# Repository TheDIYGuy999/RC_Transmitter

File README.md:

# This is an Arduino 2.4GHz radio and IR transmitter for Atmel AVR
## Features:
- IR transmitter for "LEGO" Powerfunctions and trains as well as for "MECCANO" motors
- 2.4GHz radio transmitter for RC cars, helicopters etc.
- 4 analog axes, 2 mode switches (joystick buttons)
- 1 potentiometer for adjustments like the MRSC stability control
- 4 push buttons for transmission mode and vehicle selection as well as menu navigation
- 20 seletcable vehicle addresses, so you can use it for more than one vehicle
- 3.3V, 8MHz Pro Mini (a Pro Micro is not supported anymore due to additional functionality)
- STM32 ARM version (deprecated) see: https://github.com/TheDIYGuy999/RC_Transmitter_STM32
- 2.4GHz NRF24L01 radio module
- Support for 0.96" I2C OLED
- Configuration menu for: Channel direction reversing, servo travel adjustment (independent for each vehicle)
- Configuration values are stored in EEPROM
- NRF24L01+PA+LNA SMA radio modules with power amplifier are supported from board version 1.1
- very compact
- Eagle PCB included
- PONG Game included

## Changelog:

New in V 1.3:
- Infrared codes for "MECCANO" IR controlled motors. Separate library required: https://github.com/TheDIYGuy999/MeccanoIr
- Multichannel transmission

New in V 1.4:
- 10 vehicle addresses instead of 5
- The "BACK" button can now be used (if the menu screen is not displayed on the OLED) as a momentary button, for example for a horn on the vehicle. It is sent as "data.momentary1"
- The "A6" potentiometer connector is now integrated in the code and is sent to the vehicle as "data.pot1"
- SimpleTimer library replaced with my own code, which uses significantly less memory
- EEPROM reset function added: press "Select" and "Back" during power on

New in V 1.41:
- Transmitter battery voltage now monitored correctly on 16MHz / 5V systems

New in V 1.42:
- Vehicle battery state change OLED bug fixed

New in V 1.43:
- Radio module sleep mode active while IR mode is in use

New in V 1.5:
- MECCANO IR support enhanced. Requires MECCANO library update to V 1.1

New in V 1.6:
- Buttons locked, if not required in selected transmission mode. This ensures, that no variables can be changed "in background"
- Automatic joystick zero point calibration after transmitter was switched on. This ensures, that you always have precise zero points, even if your potentiometers are not exacltly linear.

New in V 1.7:
- Support for 2 channel car style transmitters with steering wheel
- The transmitter type can be seletced in the new "transmitterConfig.h" file
- The potentiometers in some transmitters hit the mechanical endstop before the end of the electrical range is reached. This can now be compensated with the "range" variable

New in V 1.8:
- In most car style transmitters, the reverse range of the throttle potentiometer is smaller than the forward range.
- The reverse range is now multiplied by 4, to solve this problem

New in V 1.9:
- The "RC_Tester" functionality (https://github.com/TheDIYGuy999/RC_Tester) is now intergrated
- Useful, if you have more than one transmitter. Allows to visualize all 5 analog channels of your transmitter. The radio connection can be easily tested this way.
- Press "Select" during power on. The splash screen shows "Micro RC Tester" instead of "Micro RC Transmitter" and then a graphical screen, which visualizes all analog channels
- Works fo all 10 vehicle addresses

New in V 2.0:
- You have crashed your RC car? Then just play a little PONG session on your transmitter!
- Press "Back" during power on. The transittter is then activating the game mode :-)
- Press the "Back" button again to restart the game after "Game Over" is displayed

New in V 2.01:
- A serious bug in the mapJoystick() function was found during tests with the upcomming STM32 version
- The inverse and scale functionality did not work anymore since V2.0
- The bug is now solved and you can use the adjustments menu again

New in V 2.1:
- 3CH configuration for "car style" transmitter with additional 3 position switch added
- Used for 3 speed gearbox operation, using a single pole, double throw switch, connected to pin A0. Two resistors from A0 to GND and VCC allow 3 servo positions

New in V 2.2:
- 3CH configuration for WLtoys A959 etc. based 3+1CH transmitter (CONFIG_WLTOYS) See pictures below.
- Support for 3 position double throw switches (for gearbox switching etc.) added. Use two identical resistors (ca. 20k) from GND to center pin to VCC across the switch. Define a "CH1Switch" etc. variable., if a switch instead a potentiometer is connected
- New potentiometer calibration variable "reverseEndpoint" allows to adjust the throttle reverse range. Use the "Micro RC Tester" mode on a 2nd transmitter and then adjust the "range" variable as well, until the entire range of all channels is used on the graphical display.
- New "ledInversed" variable allows to use the stock WLtoys LED, which has a red and a green LED in one housing. The common pin is connected to VCC

New in V 2.3:
- 2+2CH configurarion for WLtoys transmitter added (CONFIG_WLTOYS)
- Allows to connect 3 buttons on CH4
- More than 3 buttons would be possible as well, but I ran out of space for more buttons
- Wiring see picture

New in V 2.4:
- Joystick ranges separatly adjustable for each channel in "transmitterConfig.h". This is required for the conversation of some car style transmitters, because they don't use the entire potentiometer range from end stop to end stop.

New in V 2.5:
- 20 vehicle addresses instead of 10
- Less RAM usage

New in V 2.51:
- Libraries comments added

## Usage

See pictures

3 buttons wired to CH4

3 position rocker switch wired to CH2 (for 3 speed transmission)

(c) 2016-2020 TheDIYGuy999

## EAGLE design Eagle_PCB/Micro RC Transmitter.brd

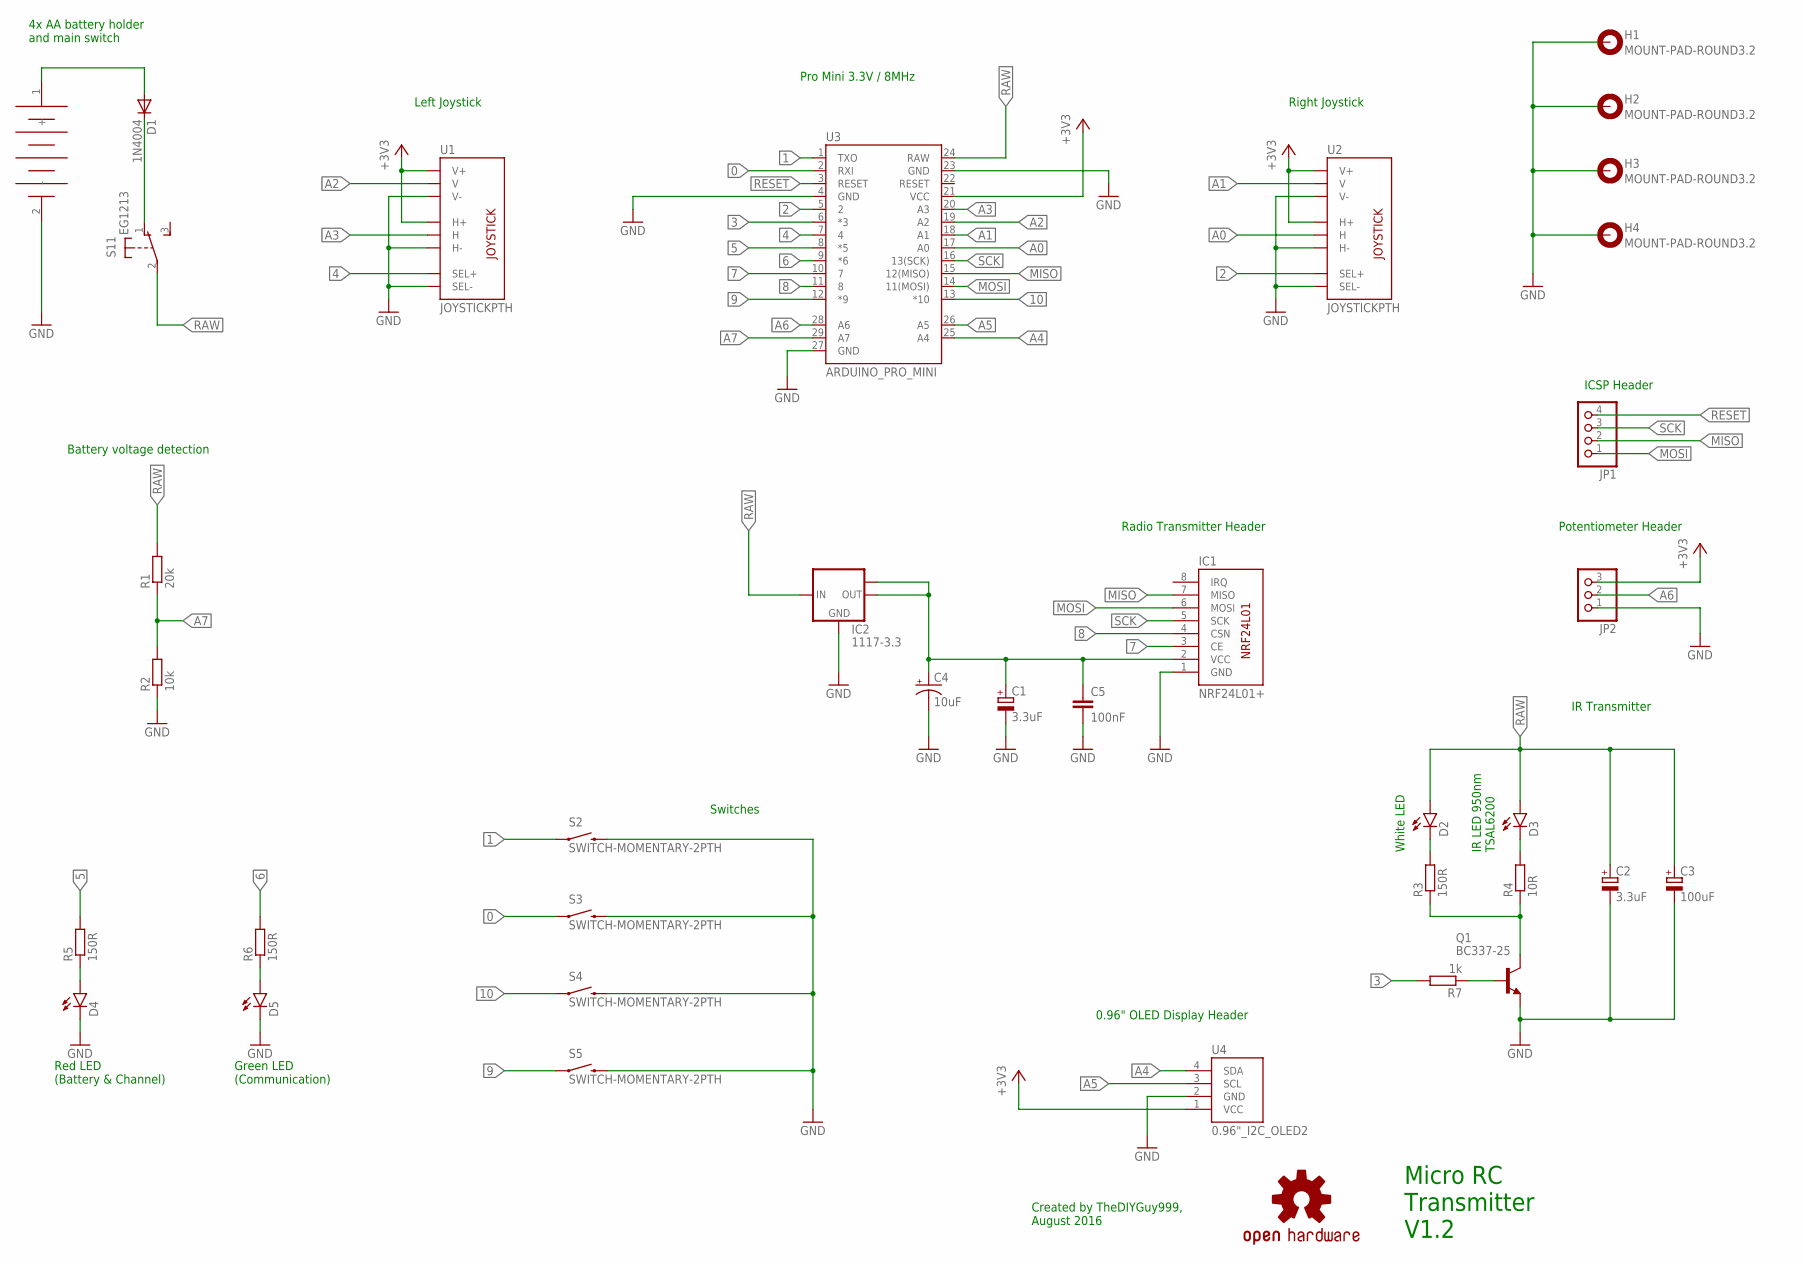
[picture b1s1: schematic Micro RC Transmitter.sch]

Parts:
C1, C2: 3.3uF; B45181A
C3: 100uF; E2,5-7
C4: 10uF; EIA3216
C5: 100nF; C0805
D1: 1N4004; DO41-10
D2, D3: LED5MM
D4, D5: LED3MM
G1: 4X_AA_BATTERY_HOLDER
H1, H2, H3, H4: MOUNT-PAD-ROUND3.2; 3,2-PAD
IC1: NRF24L01+; NRF24L01
IC2: 1117-3.3; SOT223
JP1: PINHD-1X4; 1X04
JP2: PINHD-1X3; 1X03
LOGO1: OSHW-LOGOM; OSHW-LOGO-M
Q1: BC337-25; TO92
R1: 20k; 0207/10
R2: 10k; 0207/10
R3, R5, R6: 150R; 0207/10
R4: 10R; 0207/10
R7: 1k; 0207/10
S1: EG1213
S2, S3, S4, S5: SWITCH-MOMENTARY-2PTH; TACTILE-PTH
U1, U2: JOYSTICKPTH; JOYSTICK
U3: ARDUINO_PRO_MINI
U4: 0.96"_I2C_OLED2; 0.96"_I2C_OLED_2

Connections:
0: S3.1, U3.2 (RXI)
1: S2.1, U3.1 (TXO)
2: U2.B1A (SEL+), U3.5 (2)
3: R7.2, U3.6 (*3)
4: U1.B1A (SEL+), U3.7 (4)
5: R5.2, U3.8 (*5)
6: R6.2, U3.9 (*6)
7: IC1.3 (CE), U3.10 (7)
8: IC1.4 (CSN), U3.11 (8)
9: S5.1, U3.12 (*9)
10: S4.1, U3.13 (*10)
+3V3: JP2.3, U1.H1 (H+), U1.V1 (V+), U2.H1 (H+), U2.V1 (V+), U3.21 (VCC), U4.1 (VCC)
A0: U2.H2 (H), U3.17 (A0)
A1: U2.V2 (V), U3.18 (A1)
A2: U1.V2 (V), U3.19 (A2)
A3: U1.H2 (H), U3.20 (A3)
A4: U3.25 (A4), U4.4 (SDA)
A5: U3.26 (A5), U4.3 (SCL)
A6: JP2.2, U3.28 (A6)
A7: R1.1, R2.2, U3.29 (A7)
GND: C1.-, C2.-, C3.-, C4.C (-), C5.2, D4.K (C), D5.K (C), G1.2 (-), H1.B3,2, H2.B3,2, H3.B3,2, H4.B3,2, IC1.1 (GND), IC2.1 (GND), JP2.1, Q1.1 (E), R2.1, S2.3 (2), S3.3 (2), S4.3 (2), S5.3 (2), U1.B2A (SEL-), U1.H3 (H-), U1.V3 (V-), U2.B2A (SEL-), U2.H3 (H-), U2.V3 (V-), U3.4 (GND), U3.23 (GND), U3.27 (GND), U4.2 (GND)
MISO: IC1.7 (MISO), JP1.2, U3.15 (12(MISO))
MOSI: IC1.6 (MOSI), JP1.1, U3.14 (11(MOSI))
unnamed: D4.A, R5.1
unnamed: D5.A, R6.1
unnamed: Q1.3 (C), R3.1, R4.1
unnamed: D3.K (C), R4.2
unnamed: Q1.2 (B), R7.1
unnamed: D2.K (C), R3.2
unnamed: D1.A, G1.1 (+)
unnamed: D1.C, S1.1 (O)
unnamed: C1.+, C4.A (+), C5.1, IC1.2 (VCC), IC2.2 (OUT), IC2.TAB (OUT1)
RAW: C2.+, C3.+, D2.A, D3.A, IC2.3 (IN), R1.2, S1.2, U3.24 (RAW)
RESET: JP1.4, U3.3 (RESET)
SCK: IC1.5 (SCK), JP1.3, U3.16 (13(SCK))

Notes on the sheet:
Red LED (Battery & Channel)
Green LED (Communication)
Micro RC Transmitter V1.2
White LED
IR LED 950nm TSAL6200
IR Transmitter
Radio Transmitter Header
4x AA battery holder and main switch
Left Joystick
Right Joystick
0.96" OLED Display Header
Battery voltage detection
Switches
ICSP Header
Pro Mini 3.3V / 8MHz
Potentiometer Header
Created by TheDIYGuy999, August 2016

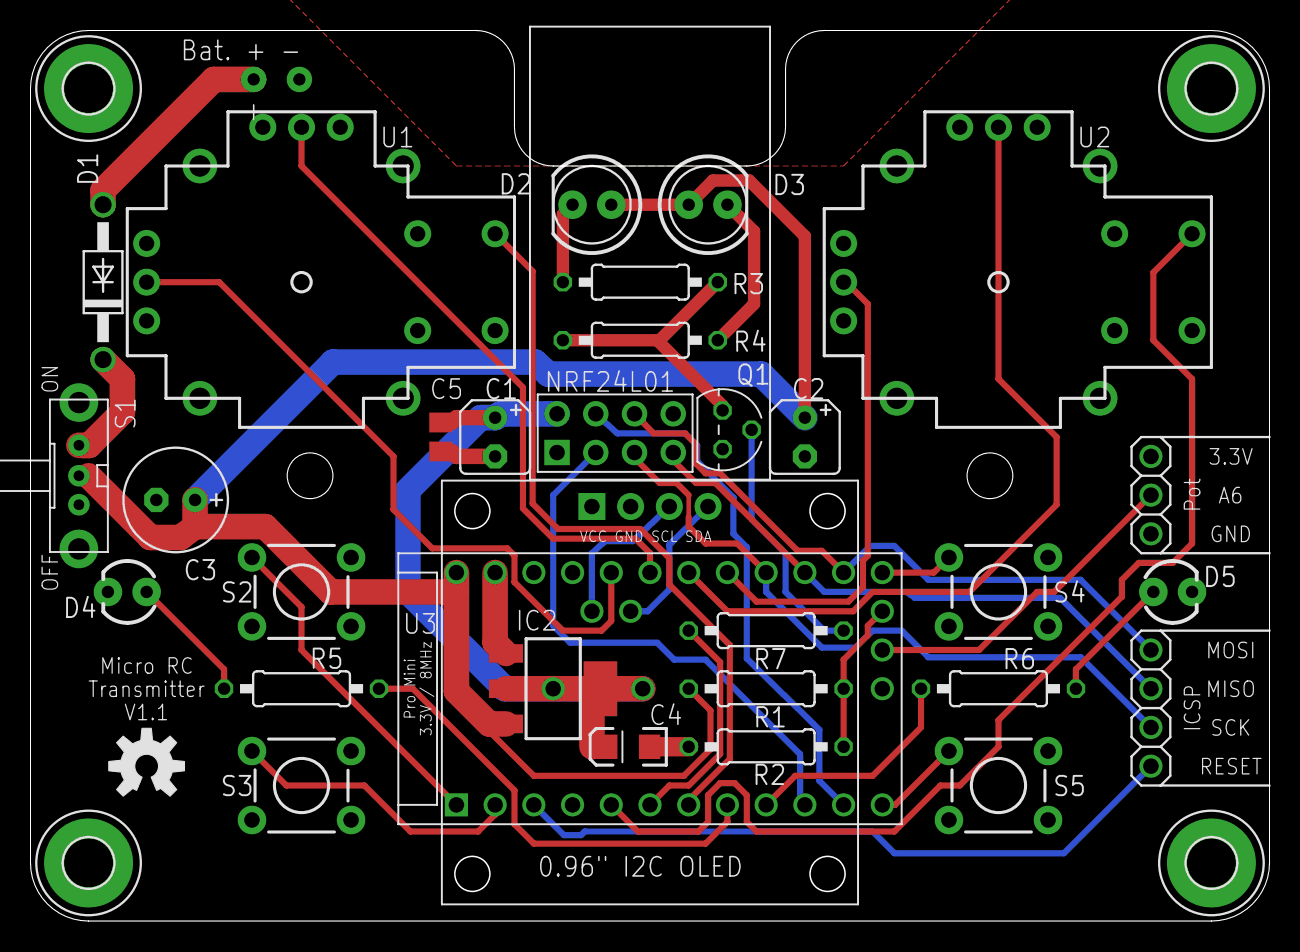
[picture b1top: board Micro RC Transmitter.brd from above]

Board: 2 copper layers, 81.2 x 58.3 mm, 37 parts (1 on the bottom side), 35 nets.

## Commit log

2016-08-06 Backchannel added, support for OLED display
2016-08-07 Schematic added
2016-08-07 New comments
2016-08-20 Create Eagle_PCB
2016-08-20 Pinout changed for final PCB
2016-08-20 Initial PCB
2016-08-20 Pic of the completed transmitter
2016-08-20 enhanced
2016-09-03 V1.1: Channel direction reversing menu added
    Independent for each vehicle. Configuration is stored in EEPROM
2016-09-05 New board revision 1.2
    separate voltage regulator for NRF24L01 radio transmitter. Allows to use a a model with power amplifier.
2016-09-05 German user manual added
    This is for SW version 1.1
2016-09-10 V1.2: Configuration menu enhanced with servo travel adjustment
2016-09-15 LED resistor values increased
2016-09-15 Version 1.21 with different transmission power levels, depending on board version
2016-09-16 German Manual for SW Version 1.2x
2016-09-22 Multiplayer fix
2016-10-02 IR code for "MECCANO" motors added. Multichannel transmission.
2016-10-04 New V1.4
2016-10-08 V1.41: Battery voltage now indicated correctly on 5V systems
2016-11-05 V1.42: Vehicle battery state change OLED bug fixed
2016-11-16 V1.43: radio in sleep mode during IR transmission mode
2016-11-17 V1.5: MECCANO IR functionality enhanced
2016-11-18 German Manual for Software V1.5
2016-11-19 V 1.6: automatic joystick calibration
2016-11-19 German Manual for Software V1.6
2016-11-26 V1.6
2017-01-17 Version changed to 1.1. 1.2 was wrong
2017-01-17 English manual for SW V1.6x
2017-01-17 Deutsche Betriebsanleitung für SW V1.6x
2017-04-27 V1.7: support for 2CH car style transmitters with steering wheel
2017-05-22 V1.8: 2CH car style transmitter support enhanced
2017-10-22 V1.9: The "RC Tester" functionality is now integrated
2017-10-22 Manual for software V1.9
2017-11-12 Picture added
2017-11-21 Manual for software V2.0
2017-11-21 V2.0: A PONG game is now included
2017-12-05 PCB picture added
2017-12-10 V2.01: bug in mapJoystick() solved
2017-12-14 V2.01: comments cleaned up
2018-05-14 Create Test
2018-05-14 STL data for 3D printing
2019-02-22 hex files for 4CH version added as requested
2019-04-09 V2.1: new 3CH configuration
    for additional 3 position switch on pin A0
2019-04-09 V2.1: new 3CH configuration
    for 3 position switch on pin A0
2019-04-09 V2.1: new 3CH configuration
2019-06-30 V2.2: Support for WLtoys based transmitter added
2020-04-18 v2.3: support for buttons on CH4 added
2021-01-03 v2.5: 20 vehicle addresses instead of 10, less RAM usage
2021-02-11 v2.51: Libraries comments added

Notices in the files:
parts and their libraries:
SparkFun-Electromechanical: Licensing: Creative Commons ShareAlike 4.0 International - https://creativecommons.org/licenses/by-sa/4.0
